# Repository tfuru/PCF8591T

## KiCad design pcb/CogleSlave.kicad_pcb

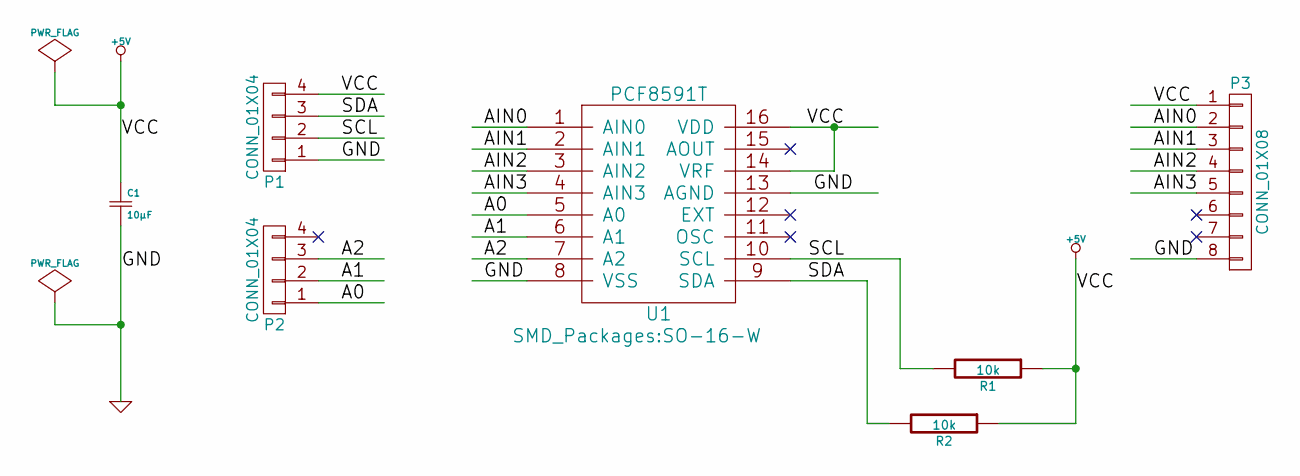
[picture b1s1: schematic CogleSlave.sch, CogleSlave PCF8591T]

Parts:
C1: 10μF; c_1206
P1, P2: CONN_01X04; Pin_Header_Straight_1x04
P3: CONN_01X08; Pin_Header_Angled_1x08
R1, R2: 10k; R_1206_HandSoldering
U1: PCF8591T; SO-16-W

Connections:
+5V: C1.1, P1.4, P3.1, R1.1, R2.1, U1.14 (VRF), U1.16 (VDD)
/A0: P2.1, U1.5 (A0)
/A1: P2.2, U1.6 (A1)
/A2: P2.3, U1.7 (A2)
/AIN0: P3.2, U1.1 (AIN0)
/AIN1: P3.3, U1.2 (AIN1)
/AIN2: P3.4, U1.3 (AIN2)
/AIN3: P3.5, U1.4 (AIN3)
/AOUT: P3.6, U1.15 (AOUT)
/SCL: P1.2, R1.2, U1.10 (SCL)
/SDA: P1.3, R2.2, U1.9 (SDA)
GND: C1.2, P1.1, P3.8, U1.8 (VSS), U1.13 (AGND)

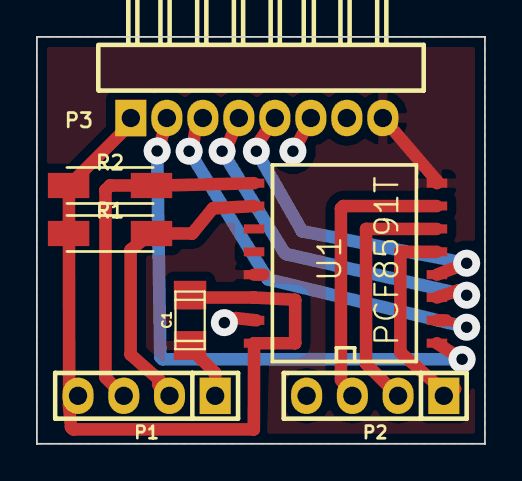
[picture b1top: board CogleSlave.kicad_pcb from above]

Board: 2 copper layers, 24.9 x 22.6 mm, 7 parts (0 on the bottom side), 12 nets.

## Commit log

2015-07-13 基板レイアウトを修正 1.2
2015-07-18 Arduino向けライブラリv1.0を追加
